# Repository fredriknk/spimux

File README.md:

# spimux

 <!-- 3D rendered pretty view -->

INFO INFO

[PCB layout](./DOCUMENTATION/spimux_board_prints.pdf) <!-- PDFs of boards -->
[SCHEMATIC](./DOCUMENTATION/spimux_schematic.pdf) <!-- Schematic PDFs -->

## FRONT

## BACK

## SIDE

# Before major commmits
Remember to run generate_outputs.bat/sh
to update the outputs and pictures.
readmetemplate

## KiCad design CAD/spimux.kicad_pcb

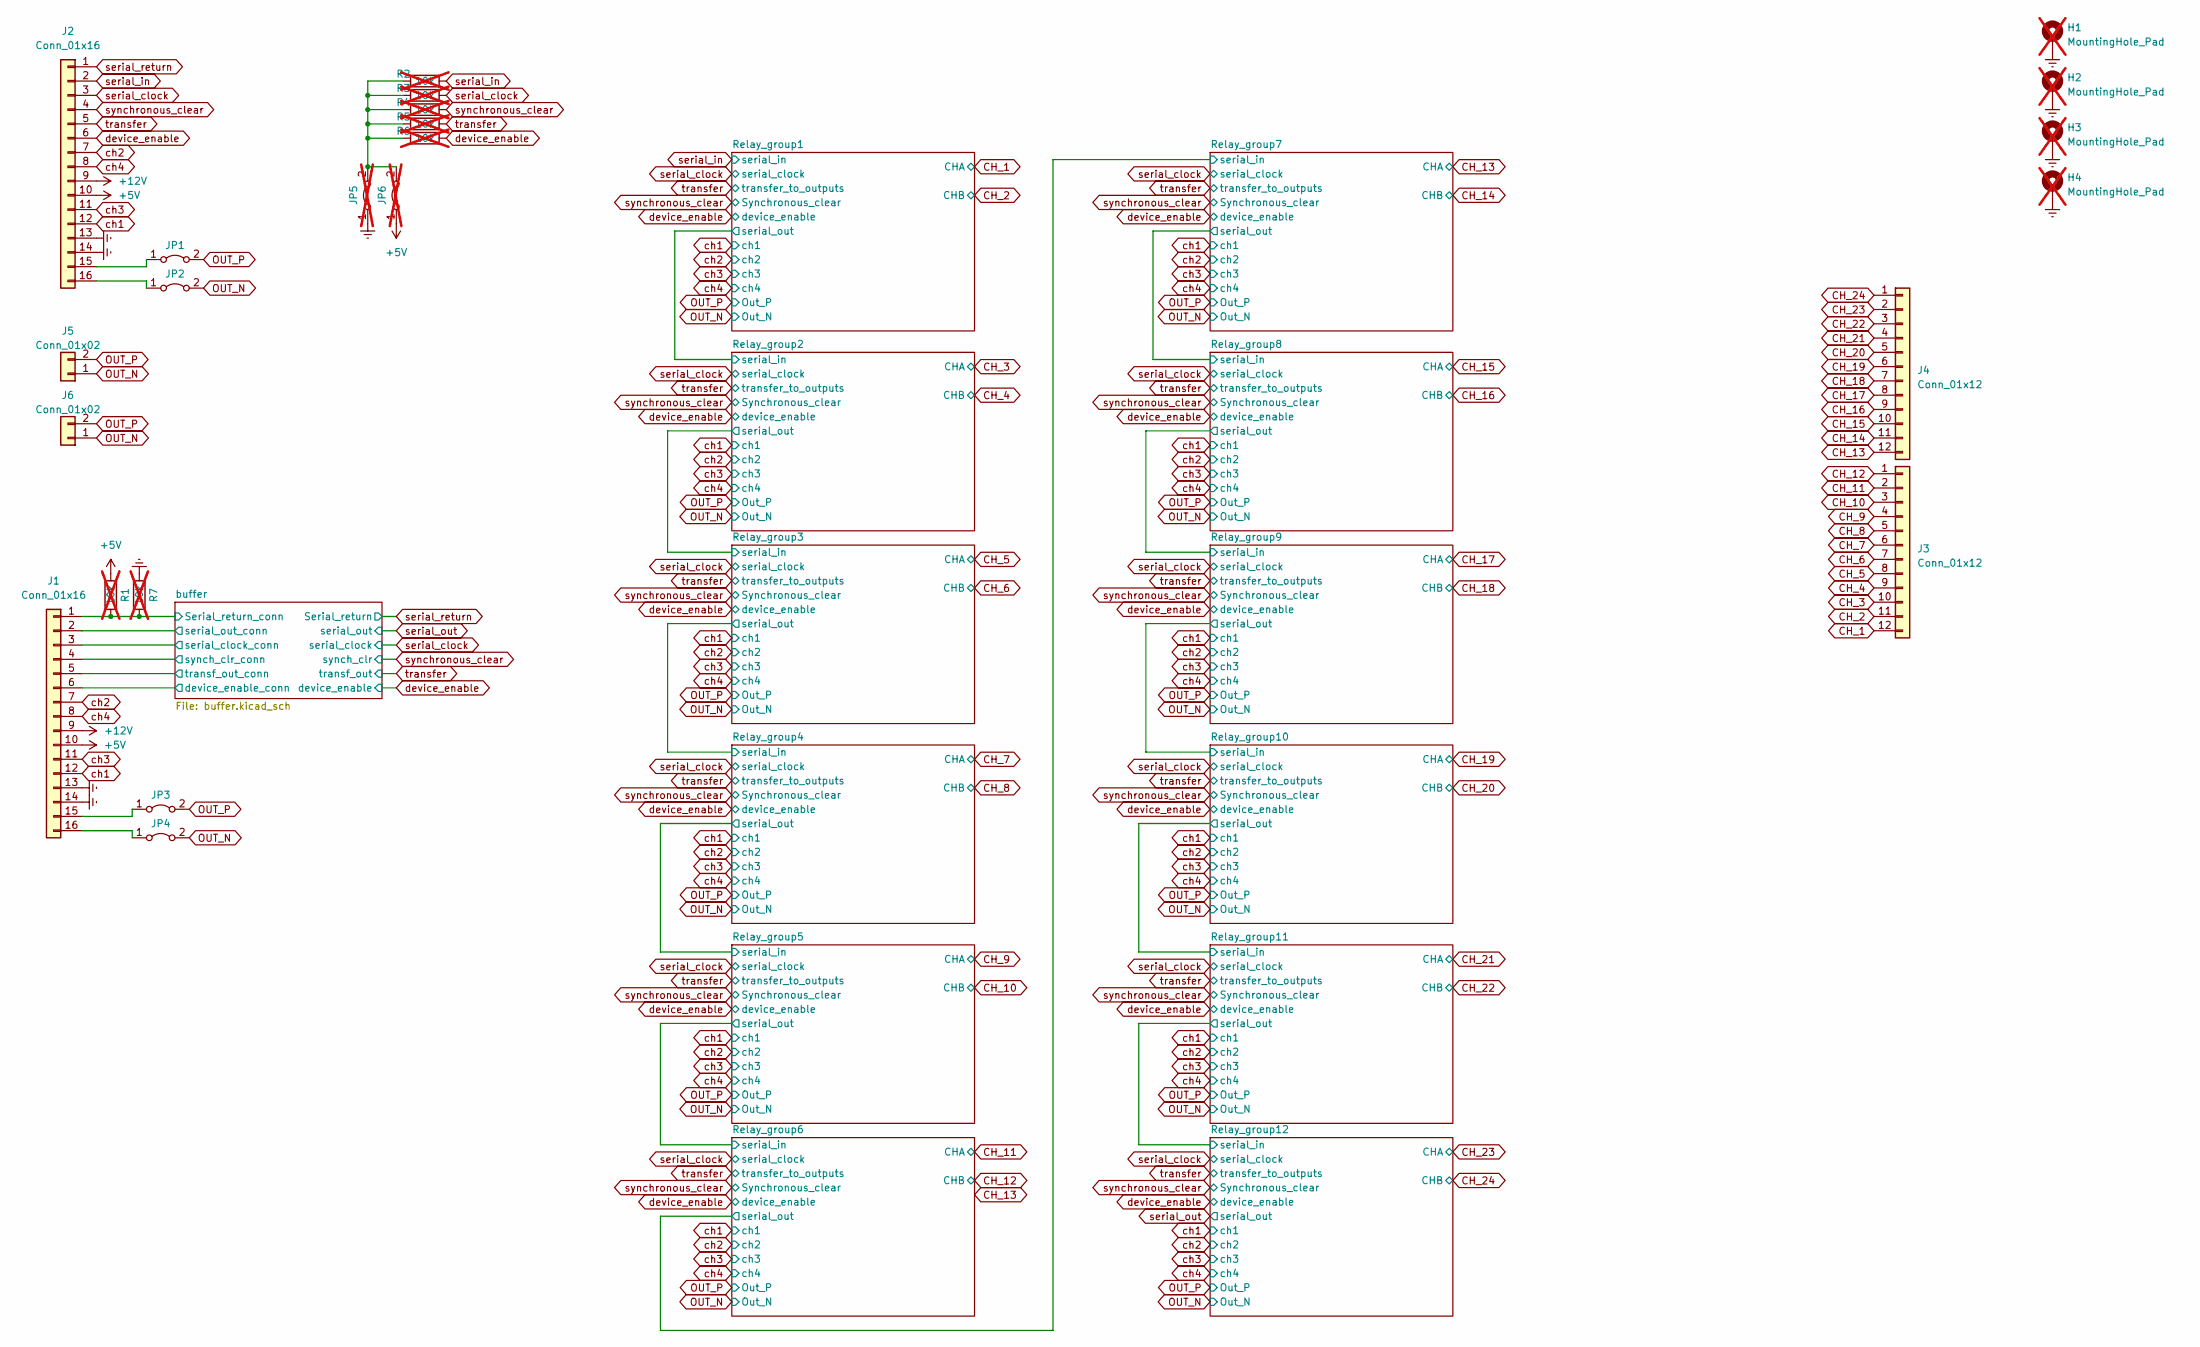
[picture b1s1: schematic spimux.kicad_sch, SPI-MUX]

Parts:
H1, H2, H3, H4: MountingHole_Pad; MountingHole_3.2mm_M3_Pad_Via; MPN NP; not fitted
J1, J2: Conn_01x16; IDC-Header_2x08_P2.54mm_Horizontal; MPN 3020-16-0200-00
J3, J4: Conn_01x12; New_PhoenixContact_MC_1,5_12-GF-5.08_1x12_P5.08mm_Horizonta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; MPN 1757349
J5, J6: Conn_01x02; New_PhoenixContact_MC_1,5_2-G-5.08_1x02_P5.08mm_Horizontal; MPN 1757242
JP1, JP2, JP3, JP4: Jumper_2_Bridged; R_0805_2012Metric; MPN 0805 0R JP
JP5, JP6: Jumper_2_Bridged; R_0603_1608Metric; MPN 0603 0R JP; not fitted
R1, R2, R3, R4, R5, R6, R7: 10k; R_0603_1608Metric; MPN 0603 10k 1%; not fitted

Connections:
+5V: J1.10, J2.10, JP6.1 (A), R1.1; also elsewhere on the board
+12V: J1.9, J2.9; also elsewhere on the board
/buffer/Serial_return_conn: J1.1, R1.2, R7.2; also elsewhere on the board
/buffer/device_enable_conn: J1.6; also elsewhere on the board
/buffer/serial_clock_conn: J1.3; also elsewhere on the board
/buffer/serial_out_conn: J1.2; also elsewhere on the board
/buffer/synch_clr_conn: J1.4; also elsewhere on the board
/buffer/transf_out_conn: J1.5; also elsewhere on the board
CH_1: J3.12; also elsewhere on the board
CH_2: J3.11; also elsewhere on the board
CH_3: J3.10; also elsewhere on the board
CH_4: J3.9; also elsewhere on the board
CH_5: J3.8; also elsewhere on the board
CH_6: J3.7; also elsewhere on the board
CH_7: J3.6; also elsewhere on the board
CH_8: J3.5; also elsewhere on the board
CH_9: J3.4; also elsewhere on the board
CH_10: J3.3; also elsewhere on the board
CH_11: J3.2; also elsewhere on the board
CH_12: J3.1; also elsewhere on the board
CH_13: J4.12; also elsewhere on the board
CH_14: J4.11; also elsewhere on the board
CH_15: J4.10; also elsewhere on the board
CH_16: J4.9; also elsewhere on the board
CH_17: J4.8; also elsewhere on the board
CH_18: J4.7; also elsewhere on the board
CH_19: J4.6; also elsewhere on the board
CH_20: J4.5; also elsewhere on the board
CH_21: J4.4; also elsewhere on the board
CH_22: J4.3; also elsewhere on the board
CH_23: J4.2; also elsewhere on the board
CH_24: J4.1; also elsewhere on the board
Earth: H1.1, H2.1, H3.1, H4.1, J1.13, J1.14, J2.13, J2.14, JP5.1 (A), R7.1; also elsewhere on the board
unnamed: J1.15, JP3.1 (A)
unnamed: J1.16, JP4.1 (A)
unnamed: J2.15, JP1.1 (A)
unnamed: J2.16, JP2.1 (A)
unnamed: JP5.2 (B), JP6.2 (B), R2.1, R3.1, R4.1, R5.1, R6.1
OUT_N: J5.1, J6.1, JP2.2 (B), JP4.2 (B); also elsewhere on the board
OUT_P: J5.2, J6.2, JP1.2 (B), JP3.2 (B); also elsewhere on the board
ch1: J1.12, J2.12; also elsewhere on the board
ch2: J1.7, J2.7; also elsewhere on the board
ch3: J1.11, J2.11; also elsewhere on the board
ch4: J1.8, J2.8; also elsewhere on the board
device_enable: J2.6, R6.2; also elsewhere on the board
serial_clock: J2.3, R3.2; also elsewhere on the board
serial_in: J2.2, R2.2; also elsewhere on the board
serial_return: J2.1; also elsewhere on the board
synchronous_clear: J2.4, R4.2; also elsewhere on the board
transfer: J2.5, R5.2; also elsewhere on the board

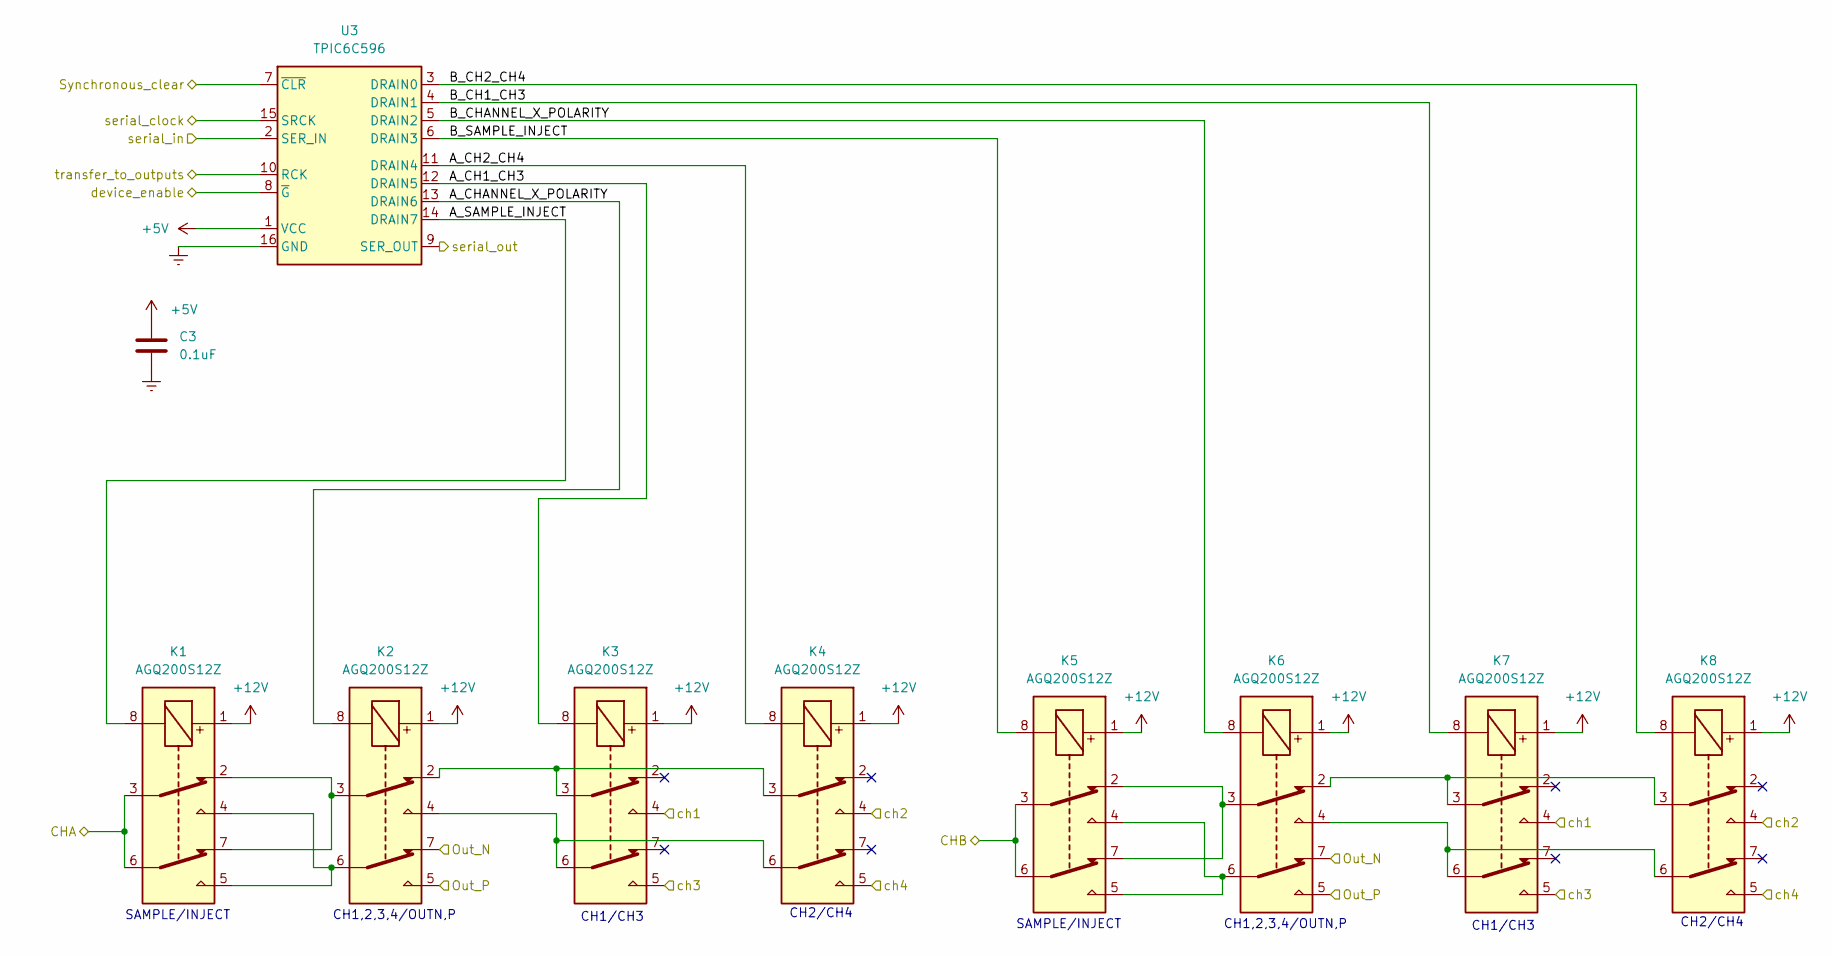
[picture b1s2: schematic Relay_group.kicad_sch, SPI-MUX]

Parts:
C3: 0.1uF; C_0603_1608Metric; MPN 0603 100nF 24v
K1, K2, K3, K4, K5, K6, K7, K8: AGQ200S12Z; Relay_2P2T_10x6mm_TE_IMxxG; MPN AGQ200S12Z
U3: TPIC6C596; TSSOP-16_4.4x5mm_P0.65mm; MPN TPIC6C596PWR

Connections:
+5V: C3.1, U3.1 (VCC); also elsewhere on the board
+12V: K1.1, K2.1, K3.1, K4.1, K5.1, K6.1, K7.1, K8.1; also elsewhere on the board
/Relay_group1/A_CH1_CH3: K3.8, U3.12 (DRAIN5)
/Relay_group1/A_CH2_CH4: K4.8, U3.11 (DRAIN4)
/Relay_group1/A_CHANNEL_X_POLARITY: K2.8, U3.13 (DRAIN6)
/Relay_group1/A_SAMPLE_INJECT: K1.8, U3.14 (DRAIN7)
/Relay_group1/B_CH1_CH3: K7.8, U3.4 (DRAIN1)
/Relay_group1/B_CH2_CH4: K8.8, U3.3 (DRAIN0)
/Relay_group1/B_CHANNEL_X_POLARITY: K6.8, U3.5 (DRAIN2)
/Relay_group1/B_SAMPLE_INJECT: K5.8, U3.6 (DRAIN3)
/Relay_group1/serial_out: U3.9 (SER_OUT); also elsewhere on the board
CH_1: K1.3, K1.6; also elsewhere on the board
CH_2: K5.3, K5.6; also elsewhere on the board
Earth: C3.2, U3.16 (GND); also elsewhere on the board
unnamed: K1.2, K1.7, K2.3
unnamed: K1.4, K1.5, K2.6
unnamed: K2.2, K3.3, K4.3
unnamed: K2.4, K3.6, K4.6
unnamed: K5.2, K5.7, K6.3
unnamed: K5.4, K5.5, K6.6
unnamed: K6.2, K7.3, K8.3
unnamed: K6.4, K7.6, K8.6
OUT_N: K2.7, K6.7; also elsewhere on the board
OUT_P: K2.5, K6.5; also elsewhere on the board
ch1: K3.4, K7.4; also elsewhere on the board
ch2: K4.4, K8.4; also elsewhere on the board
ch3: K3.5, K7.5; also elsewhere on the board
ch4: K4.5, K8.5; also elsewhere on the board
device_enable: U3.8 (~G); also elsewhere on the board
serial_clock: U3.15 (SRCK); also elsewhere on the board
serial_in: U3.2 (SER_IN); also elsewhere on the board
synchronous_clear: U3.7 (~CLR); also elsewhere on the board
transfer: U3.10 (RCK); also elsewhere on the board

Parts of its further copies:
C4, C5, C6, C7, C8, C9, C10, C11, C12, C13, C14: 0.1uF; C_0603_1608Metric; MPN 0603 100nF 24v
K9, K10, K11, K12, K13, K14, K15, K16, K17, K18, K19, K20, K21, K22, K23, K24, K25, K26, K27, K28, K29, K30, K31, K32, K33, K34, K35, K36, K37, K38, K39, K40, K41, K42, K43, K44, K45, K46, K47, K48, K49, K50, K51, K52, K53, K54, K55, K56, K57, K58, K59, K60, K61, K62, K63, K64, K65, K66, K67, K68, K69, K70, K71, K72, K73, K74, K75, K76, K77, K78, K79, K80, K81, K82, K83, K84, K85, K86, K87, K88, K89, K90, K91, K92, K93, K94, K95, K96: AGQ200S12Z; Relay_2P2T_10x6mm_TE_IMxxG; MPN AGQ200S12Z
U4, U5, U6, U7, U8, U9, U10, U11, U12, U13, U14: TPIC6C596; TSSOP-16_4.4x5mm_P0.65mm; MPN TPIC6C596PWR

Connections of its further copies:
+5V: C4.1, C5.1, C6.1, C7.1, C8.1, C9.1, C10.1, C11.1, C12.1, C13.1, C14.1, U4.1 (VCC), U5.1 (VCC), U6.1 (VCC), U7.1 (VCC), U8.1 (VCC), U9.1 (VCC), U10.1 (VCC), U11.1 (VCC), U12.1 (VCC), U13.1 (VCC), U14.1 (VCC); also elsewhere on the board
+12V: K9.1, K10.1, K11.1, K12.1, K13.1, K14.1, K15.1, K16.1, K17.1, K18.1, K19.1, K20.1, K21.1, K22.1, K23.1, K24.1, K25.1, K26.1, K27.1, K28.1, K29.1, K30.1, K31.1, K32.1, K33.1, K34.1, K35.1, K36.1, K37.1, K38.1, K39.1, K40.1, K41.1, K42.1, K43.1, K44.1, K45.1, K46.1, K47.1, K48.1, K49.1, K50.1, K51.1, K52.1, K53.1, K54.1, K55.1, K56.1, K57.1, K58.1, K59.1, K60.1, K61.1, K62.1, K63.1, K64.1, K65.1, K66.1, K67.1, K68.1, K69.1, K70.1, K71.1, K72.1, K73.1, K74.1, K75.1, K76.1, K77.1, K78.1, K79.1, K80.1, K81.1, K82.1, K83.1, K84.1, K85.1, K86.1, K87.1, K88.1, K89.1, K90.1, K91.1, K92.1, K93.1, K94.1, K95.1, K96.1; also elsewhere on the board
/Relay_group1/serial_out: U4.2 (SER_IN); also elsewhere on the board
/Relay_group2/A_CH1_CH3: K11.8, U4.12 (DRAIN5)
/Relay_group2/A_CH2_CH4: K12.8, U4.11 (DRAIN4)
/Relay_group2/A_CHANNEL_X_POLARITY: K10.8, U4.13 (DRAIN6)
/Relay_group2/A_SAMPLE_INJECT: K9.8, U4.14 (DRAIN7)
/Relay_group2/B_CH1_CH3: K15.8, U4.4 (DRAIN1)
/Relay_group2/B_CH2_CH4: K16.8, U4.3 (DRAIN0)
/Relay_group2/B_CHANNEL_X_POLARITY: K14.8, U4.5 (DRAIN2)
/Relay_group2/B_SAMPLE_INJECT: K13.8, U4.6 (DRAIN3)
/Relay_group2/serial_out: U4.9 (SER_OUT), U5.2 (SER_IN)
/Relay_group3/A_CH1_CH3: K19.8, U5.12 (DRAIN5)
/Relay_group3/A_CH2_CH4: K20.8, U5.11 (DRAIN4)
/Relay_group3/A_CHANNEL_X_POLARITY: K18.8, U5.13 (DRAIN6)
/Relay_group3/A_SAMPLE_INJECT: K17.8, U5.14 (DRAIN7)
/Relay_group3/B_CH1_CH3: K23.8, U5.4 (DRAIN1)
/Relay_group3/B_CH2_CH4: K24.8, U5.3 (DRAIN0)
/Relay_group3/B_CHANNEL_X_POLARITY: K22.8, U5.5 (DRAIN2)
/Relay_group3/B_SAMPLE_INJECT: K21.8, U5.6 (DRAIN3)
/Relay_group3/serial_out: U5.9 (SER_OUT), U6.2 (SER_IN)
/Relay_group4/A_CH1_CH3: K27.8, U6.12 (DRAIN5)
/Relay_group4/A_CH2_CH4: K28.8, U6.11 (DRAIN4)
/Relay_group4/A_CHANNEL_X_POLARITY: K26.8, U6.13 (DRAIN6)
/Relay_group4/A_SAMPLE_INJECT: K25.8, U6.14 (DRAIN7)
/Relay_group4/B_CH1_CH3: K31.8, U6.4 (DRAIN1)
/Relay_group4/B_CH2_CH4: K32.8, U6.3 (DRAIN0)
/Relay_group4/B_CHANNEL_X_POLARITY: K30.8, U6.5 (DRAIN2)
/Relay_group4/B_SAMPLE_INJECT: K29.8, U6.6 (DRAIN3)
/Relay_group4/serial_out: U6.9 (SER_OUT), U7.2 (SER_IN)
/Relay_group5/A_CH1_CH3: K35.8, U7.12 (DRAIN5)
/Relay_group5/A_CH2_CH4: K36.8, U7.11 (DRAIN4)
/Relay_group5/A_CHANNEL_X_POLARITY: K34.8, U7.13 (DRAIN6)
/Relay_group5/A_SAMPLE_INJECT: K33.8, U7.14 (DRAIN7)
/Relay_group5/B_CH1_CH3: K39.8, U7.4 (DRAIN1)
/Relay_group5/B_CH2_CH4: K40.8, U7.3 (DRAIN0)
/Relay_group5/B_CHANNEL_X_POLARITY: K38.8, U7.5 (DRAIN2)
/Relay_group5/B_SAMPLE_INJECT: K37.8, U7.6 (DRAIN3)
/Relay_group5/serial_out: U7.9 (SER_OUT), U8.2 (SER_IN)
/Relay_group6/A_CH1_CH3: K43.8, U8.12 (DRAIN5)
/Relay_group6/A_CH2_CH4: K44.8, U8.11 (DRAIN4)
/Relay_group6/A_CHANNEL_X_POLARITY: K42.8, U8.13 (DRAIN6)
/Relay_group6/A_SAMPLE_INJECT: K41.8, U8.14 (DRAIN7)
/Relay_group6/B_CH1_CH3: K47.8, U8.4 (DRAIN1)
/Relay_group6/B_CH2_CH4: K48.8, U8.3 (DRAIN0)
/Relay_group6/B_CHANNEL_X_POLARITY: K46.8, U8.5 (DRAIN2)
/Relay_group6/B_SAMPLE_INJECT: K45.8, U8.6 (DRAIN3)
/Relay_group6/serial_out: U8.9 (SER_OUT), U9.2 (SER_IN)
/Relay_group7/A_CH1_CH3: K51.8, U9.12 (DRAIN5)
/Relay_group7/A_CH2_CH4: K52.8, U9.11 (DRAIN4)
/Relay_group7/A_CHANNEL_X_POLARITY: K50.8, U9.13 (DRAIN6)
/Relay_group7/A_SAMPLE_INJECT: K49.8, U9.14 (DRAIN7)
/Relay_group7/B_CH1_CH3: K55.8, U9.4 (DRAIN1)
/Relay_group7/B_CH2_CH4: K56.8, U9.3 (DRAIN0)
/Relay_group7/B_CHANNEL_X_POLARITY: K54.8, U9.5 (DRAIN2)
/Relay_group7/B_SAMPLE_INJECT: K53.8, U9.6 (DRAIN3)
/Relay_group7/serial_out: U9.9 (SER_OUT), U10.2 (SER_IN)
/Relay_group8/A_CH1_CH3: K59.8, U10.12 (DRAIN5)
/Relay_group8/A_CH2_CH4: K60.8, U10.11 (DRAIN4)
/Relay_group8/A_CHANNEL_X_POLARITY: K58.8, U10.13 (DRAIN6)
/Relay_group8/A_SAMPLE_INJECT: K57.8, U10.14 (DRAIN7)
/Relay_group8/B_CH1_CH3: K63.8, U10.4 (DRAIN1)
/Relay_group8/B_CH2_CH4: K64.8, U10.3 (DRAIN0)
/Relay_group8/B_CHANNEL_X_POLARITY: K62.8, U10.5 (DRAIN2)
/Relay_group8/B_SAMPLE_INJECT: K61.8, U10.6 (DRAIN3)
/Relay_group8/serial_out: U10.9 (SER_OUT), U11.2 (SER_IN)
/Relay_group9/A_CH1_CH3: K67.8, U11.12 (DRAIN5)
/Relay_group9/A_CH2_CH4: K68.8, U11.11 (DRAIN4)
/Relay_group9/A_CHANNEL_X_POLARITY: K66.8, U11.13 (DRAIN6)
/Relay_group9/A_SAMPLE_INJECT: K65.8, U11.14 (DRAIN7)
/Relay_group9/B_CH1_CH3: K71.8, U11.4 (DRAIN1)
/Relay_group9/B_CH2_CH4: K72.8, U11.3 (DRAIN0)
/Relay_group9/B_CHANNEL_X_POLARITY: K70.8, U11.5 (DRAIN2)
/Relay_group9/B_SAMPLE_INJECT: K69.8, U11.6 (DRAIN3)
/Relay_group10/A_CH1_CH3: K75.8, U12.12 (DRAIN5)
/Relay_group10/A_CH2_CH4: K76.8, U12.11 (DRAIN4)
/Relay_group10/A_CHANNEL_X_POLARITY: K74.8, U12.13 (DRAIN6)
/Relay_group10/A_SAMPLE_INJECT: K73.8, U12.14 (DRAIN7)
/Relay_group10/B_CH1_CH3: K79.8, U12.4 (DRAIN1)
/Relay_group10/B_CH2_CH4: K80.8, U12.3 (DRAIN0)
/Relay_group10/B_CHANNEL_X_POLARITY: K78.8, U12.5 (DRAIN2)
/Relay_group10/B_SAMPLE_INJECT: K77.8, U12.6 (DRAIN3)
/Relay_group10/serial_in: U11.9 (SER_OUT), U12.2 (SER_IN)
/Relay_group10/serial_out: U12.9 (SER_OUT), U13.2 (SER_IN)
/Relay_group11/A_CH1_CH3: K83.8, U13.12 (DRAIN5)
/Relay_group11/A_CH2_CH4: K84.8, U13.11 (DRAIN4)
/Relay_group11/A_CHANNEL_X_POLARITY: K82.8, U13.13 (DRAIN6)
/Relay_group11/A_SAMPLE_INJECT: K81.8, U13.14 (DRAIN7)
/Relay_group11/B_CH1_CH3: K87.8, U13.4 (DRAIN1)
/Relay_group11/B_CH2_CH4: K88.8, U13.3 (DRAIN0)
/Relay_group11/B_CHANNEL_X_POLARITY: K86.8, U13.5 (DRAIN2)
/Relay_group11/B_SAMPLE_INJECT: K85.8, U13.6 (DRAIN3)
/Relay_group11/serial_out: U13.9 (SER_OUT), U14.2 (SER_IN)
/Relay_group12/A_CH1_CH3: K91.8, U14.12 (DRAIN5)
/Relay_group12/A_CH2_CH4: K92.8, U14.11 (DRAIN4)
/Relay_group12/A_CHANNEL_X_POLARITY: K90.8, U14.13 (DRAIN6)
/Relay_group12/A_SAMPLE_INJECT: K89.8, U14.14 (DRAIN7)
/Relay_group12/B_CH1_CH3: K95.8, U14.4 (DRAIN1)
/Relay_group12/B_CH2_CH4: K96.8, U14.3 (DRAIN0)
/Relay_group12/B_CHANNEL_X_POLARITY: K94.8, U14.5 (DRAIN2)
/Relay_group12/B_SAMPLE_INJECT: K93.8, U14.6 (DRAIN3)
CH_3: K9.3, K9.6; also elsewhere on the board
CH_4: K13.3, K13.6; also elsewhere on the board
CH_5: K17.3, K17.6; also elsewhere on the board
CH_6: K21.3, K21.6; also elsewhere on the board
CH_7: K25.3, K25.6; also elsewhere on the board
CH_8: K29.3, K29.6; also elsewhere on the board
CH_9: K33.3, K33.6; also elsewhere on the board
CH_10: K37.3, K37.6; also elsewhere on the board
CH_11: K41.3, K41.6; also elsewhere on the board
CH_12: K45.3, K45.6; also elsewhere on the board
CH_13: K49.3, K49.6; also elsewhere on the board
CH_14: K53.3, K53.6; also elsewhere on the board
CH_15: K57.3, K57.6; also elsewhere on the board
CH_16: K61.3, K61.6; also elsewhere on the board
CH_17: K65.3, K65.6; also elsewhere on the board
CH_18: K69.3, K69.6; also elsewhere on the board
CH_19: K73.3, K73.6; also elsewhere on the board
CH_20: K77.3, K77.6; also elsewhere on the board
CH_21: K81.3, K81.6; also elsewhere on the board
CH_22: K85.3, K85.6; also elsewhere on the board
CH_23: K89.3, K89.6; also elsewhere on the board
CH_24: K93.3, K93.6; also elsewhere on the board
Earth: C4.2, C5.2, C6.2, C7.2, C8.2, C9.2, C10.2, C11.2, C12.2, C13.2, C14.2, U4.16 (GND), U5.16 (GND), U6.16 (GND), U7.16 (GND), U8.16 (GND), U9.16 (GND), U10.16 (GND), U11.16 (GND), U12.16 (GND), U13.16 (GND), U14.16 (GND); also elsewhere on the board
unnamed: K10.2, K11.3, K12.3
unnamed: K9.2, K9.7, K10.3
unnamed: K10.4, K11.6, K12.6
unnamed: K9.4, K9.5, K10.6
unnamed: K13.2, K13.7, K14.3
unnamed: K13.4, K13.5, K14.6
unnamed: K14.2, K15.3, K16.3
unnamed: K14.4, K15.6, K16.6
unnamed: K17.2, K17.7, K18.3
unnamed: K17.4, K17.5, K18.6
unnamed: K18.2, K19.3, K20.3
unnamed: K18.4, K19.6, K20.6
unnamed: K21.2, K21.7, K22.3
unnamed: K21.4, K21.5, K22.6
unnamed: K22.2, K23.3, K24.3
unnamed: K22.4, K23.6, K24.6
unnamed: K25.2, K25.7, K26.3
unnamed: K25.4, K25.5, K26.6
unnamed: K26.2, K27.3, K28.3
unnamed: K26.4, K27.6, K28.6
unnamed: K29.2, K29.7, K30.3
unnamed: K29.4, K29.5, K30.6
unnamed: K30.2, K31.3, K32.3
unnamed: K30.4, K31.6, K32.6
unnamed: K33.2, K33.7, K34.3
unnamed: K33.4, K33.5, K34.6
unnamed: K34.2, K35.3, K36.3
unnamed: K34.4, K35.6, K36.6
unnamed: K37.2, K37.7, K38.3
unnamed: K37.4, K37.5, K38.6
unnamed: K38.2, K39.3, K40.3
unnamed: K38.4, K39.6, K40.6
unnamed: K41.2, K41.7, K42.3
unnamed: K41.4, K41.5, K42.6
unnamed: K42.2, K43.3, K44.3
unnamed: K42.4, K43.6, K44.6
unnamed: K45.2, K45.7, K46.3
unnamed: K45.4, K45.5, K46.6
unnamed: K46.2, K47.3, K48.3
unnamed: K46.4, K47.6, K48.6
unnamed: K49.2, K49.7, K50.3
unnamed: K49.4, K49.5, K50.6
unnamed: K50.2, K51.3, K52.3
unnamed: K50.4, K51.6, K52.6
unnamed: K53.2, K53.7, K54.3
unnamed: K53.4, K53.5, K54.6
unnamed: K54.2, K55.3, K56.3
unnamed: K54.4, K55.6, K56.6
unnamed: K57.2, K57.7, K58.3
unnamed: K57.4, K57.5, K58.6
unnamed: K58.2, K59.3, K60.3
unnamed: K58.4, K59.6, K60.6
unnamed: K61.2, K61.7, K62.3
unnamed: K61.4, K61.5, K62.6
unnamed: K62.2, K63.3, K64.3
unnamed: K62.4, K63.6, K64.6
unnamed: K65.2, K65.7, K66.3
unnamed: K65.4, K65.5, K66.6
unnamed: K66.2, K67.3, K68.3
unnamed: K66.4, K67.6, K68.6
unnamed: K69.2, K69.7, K70.3
unnamed: K69.4, K69.5, K70.6
unnamed: K70.2, K71.3, K72.3
unnamed: K70.4, K71.6, K72.6
unnamed: K73.2, K73.7, K74.3
unnamed: K73.4, K73.5, K74.6
unnamed: K74.2, K75.3, K76.3
unnamed: K74.4, K75.6, K76.6
unnamed: K77.2, K77.7, K78.3
unnamed: K77.4, K77.5, K78.6
unnamed: K78.2, K79.3, K80.3
unnamed: K78.4, K79.6, K80.6
unnamed: K81.2, K81.7, K82.3
unnamed: K81.4, K81.5, K82.6
unnamed: K82.2, K83.3, K84.3
unnamed: K82.4, K83.6, K84.6
unnamed: K85.2, K85.7, K86.3
unnamed: K85.4, K85.5, K86.6
unnamed: K86.2, K87.3, K88.3
unnamed: K86.4, K87.6, K88.6
unnamed: K89.2, K89.7, K90.3
unnamed: K89.4, K89.5, K90.6
unnamed: K90.2, K91.3, K92.3
unnamed: K90.4, K91.6, K92.6
unnamed: K93.2, K93.7, K94.3
unnamed: K93.4, K93.5, K94.6
unnamed: K94.2, K95.3, K96.3
unnamed: K94.4, K95.6, K96.6
OUT_N: K10.7, K14.7, K18.7, K22.7, K26.7, K30.7, K34.7, K38.7, K42.7, K46.7, K50.7, K54.7, K58.7, K62.7, K66.7, K70.7, K74.7, K78.7, K82.7, K86.7, K90.7, K94.7; also elsewhere on the board
OUT_P: K10.5, K14.5, K18.5, K22.5, K26.5, K30.5, K34.5, K38.5, K42.5, K46.5, K50.5, K54.5, K58.5, K62.5, K66.5, K70.5, K74.5, K78.5, K82.5, K86.5, K90.5, K94.5; also elsewhere on the board
ch1: K11.4, K15.4, K19.4, K23.4, K27.4, K31.4, K35.4, K39.4, K43.4, K47.4, K51.4, K55.4, K59.4, K63.4, K67.4, K71.4, K75.4, K79.4, K83.4, K87.4, K91.4, K95.4; also elsewhere on the board
ch2: K12.4, K16.4, K20.4, K24.4, K28.4, K32.4, K36.4, K40.4, K44.4, K48.4, K52.4, K56.4, K60.4, K64.4, K68.4, K72.4, K76.4, K80.4, K84.4, K88.4, K92.4, K96.4; also elsewhere on the board
ch3: K11.5, K15.5, K19.5, K23.5, K27.5, K31.5, K35.5, K39.5, K43.5, K47.5, K51.5, K55.5, K59.5, K63.5, K67.5, K71.5, K75.5, K79.5, K83.5, K87.5, K91.5, K95.5; also elsewhere on the board
ch4: K12.5, K16.5, K20.5, K24.5, K28.5, K32.5, K36.5, K40.5, K44.5, K48.5, K52.5, K56.5, K60.5, K64.5, K68.5, K72.5, K76.5, K80.5, K84.5, K88.5, K92.5, K96.5; also elsewhere on the board
device_enable: U4.8 (~G), U5.8 (~G), U6.8 (~G), U7.8 (~G), U8.8 (~G), U9.8 (~G), U10.8 (~G), U11.8 (~G), U12.8 (~G), U13.8 (~G), U14.8 (~G); also elsewhere on the board
serial_clock: U4.15 (SRCK), U5.15 (SRCK), U6.15 (SRCK), U7.15 (SRCK), U8.15 (SRCK), U9.15 (SRCK), U10.15 (SRCK), U11.15 (SRCK), U12.15 (SRCK), U13.15 (SRCK), U14.15 (SRCK); also elsewhere on the board
serial_out: U14.9 (SER_OUT); also elsewhere on the board
synchronous_clear: U4.7 (~CLR), U5.7 (~CLR), U6.7 (~CLR), U7.7 (~CLR), U8.7 (~CLR), U9.7 (~CLR), U10.7 (~CLR), U11.7 (~CLR), U12.7 (~CLR), U13.7 (~CLR), U14.7 (~CLR); also elsewhere on the board
transfer: U4.10 (RCK), U5.10 (RCK), U6.10 (RCK), U7.10 (RCK), U8.10 (RCK), U9.10 (RCK), U10.10 (RCK), U11.10 (RCK), U12.10 (RCK), U13.10 (RCK), U14.10 (RCK); also elsewhere on the board

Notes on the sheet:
CH1,2,3,4/OUTN,P
SAMPLE/INJECT
CH1/CH3
CH2/CH4

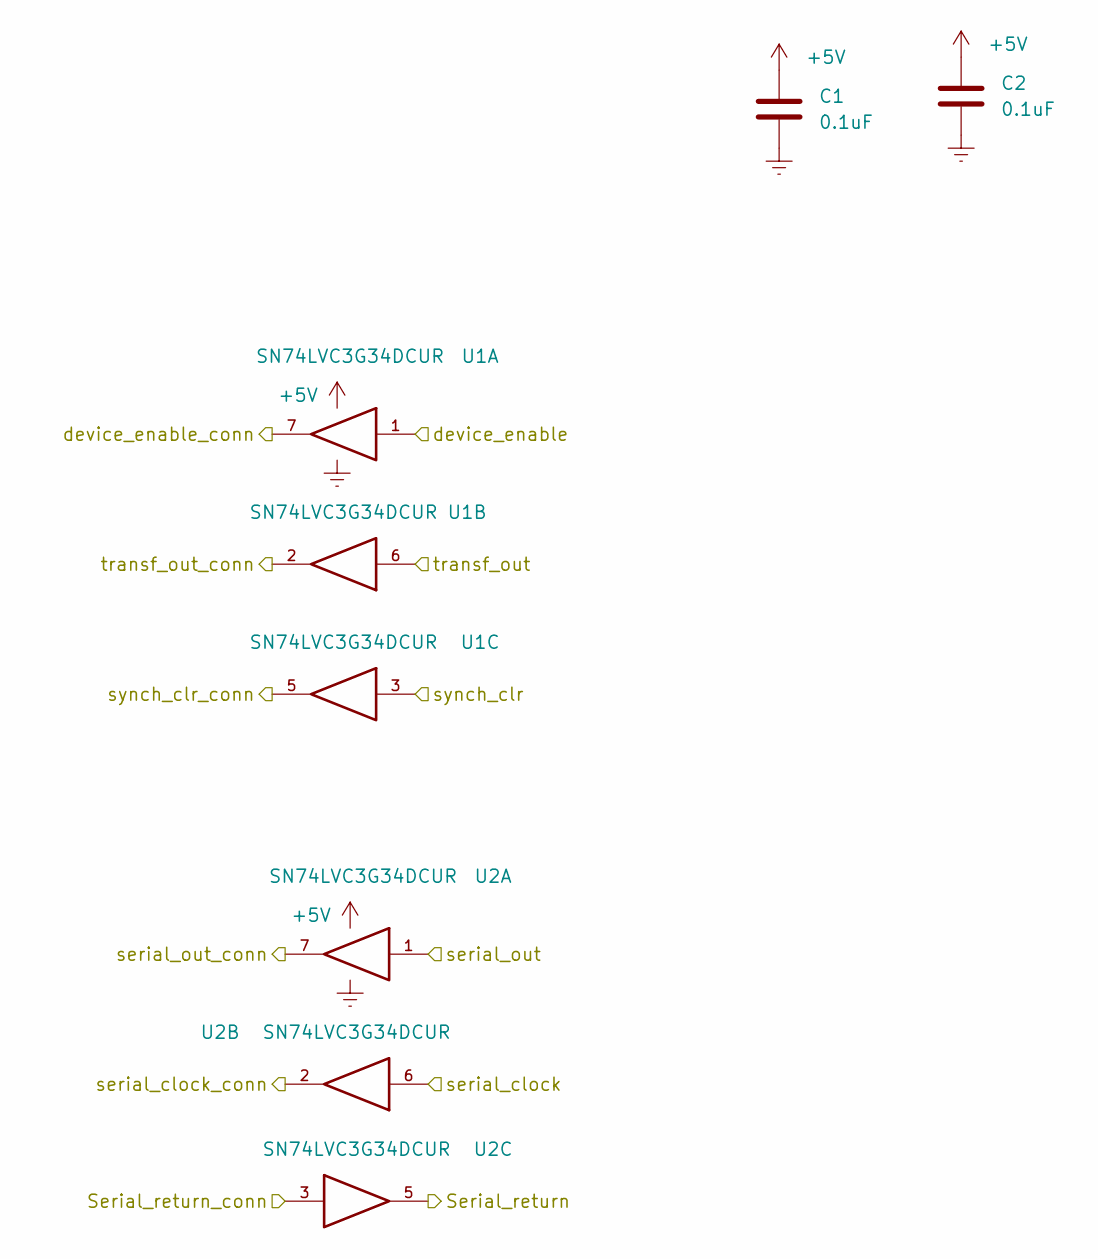
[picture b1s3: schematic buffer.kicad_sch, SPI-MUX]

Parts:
C1, C2: 0.1uF; C_0603_1608Metric; MPN 0603 100nF 24v
U1, U2: SN74LVC3G34DCUR; VSSOP-8_2.3x2mm_P0.5mm; MPN SN74LVC3G34DCUR

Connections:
+5V: C1.1, C2.1, U1.8 (VCC), U2.8 (VCC); also elsewhere on the board
/buffer/Serial_return_conn: U2.3; also elsewhere on the board
/buffer/device_enable_conn: U1.7; also elsewhere on the board
/buffer/serial_clock_conn: U2.2; also elsewhere on the board
/buffer/serial_out_conn: U2.7; also elsewhere on the board
/buffer/synch_clr_conn: U1.5; also elsewhere on the board
/buffer/transf_out_conn: U1.2; also elsewhere on the board
Earth: C1.2, C2.2, U1.4 (GND), U2.4 (GND); also elsewhere on the board
device_enable: U1.1; also elsewhere on the board
serial_clock: U2.6; also elsewhere on the board
serial_out: U2.1; also elsewhere on the board
serial_return: U2.5; also elsewhere on the board
synchronous_clear: U1.3; also elsewhere on the board
transfer: U1.6; also elsewhere on the board

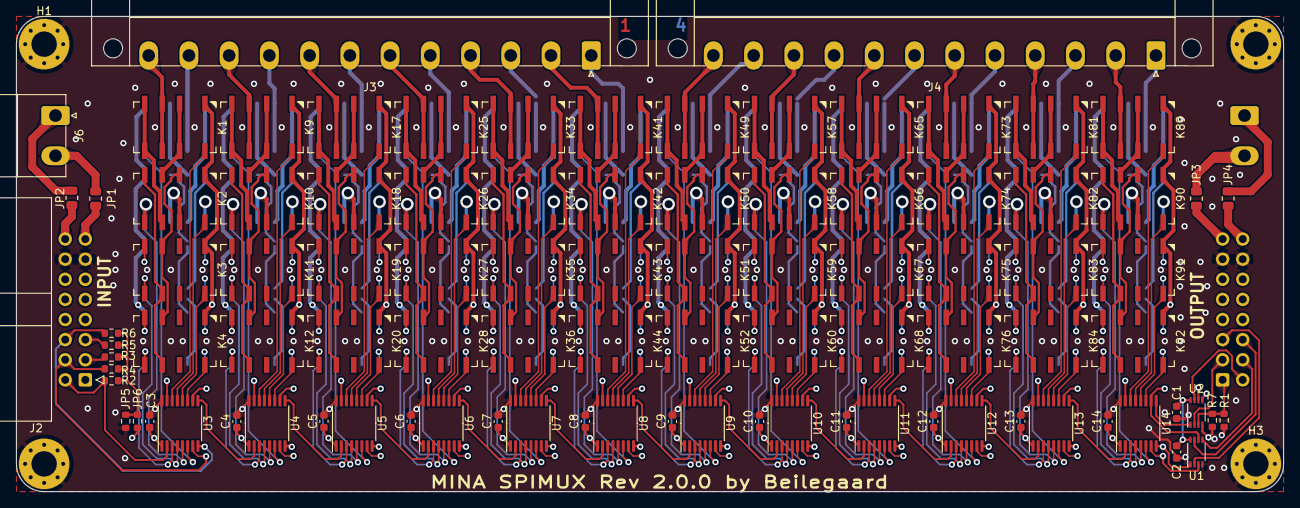
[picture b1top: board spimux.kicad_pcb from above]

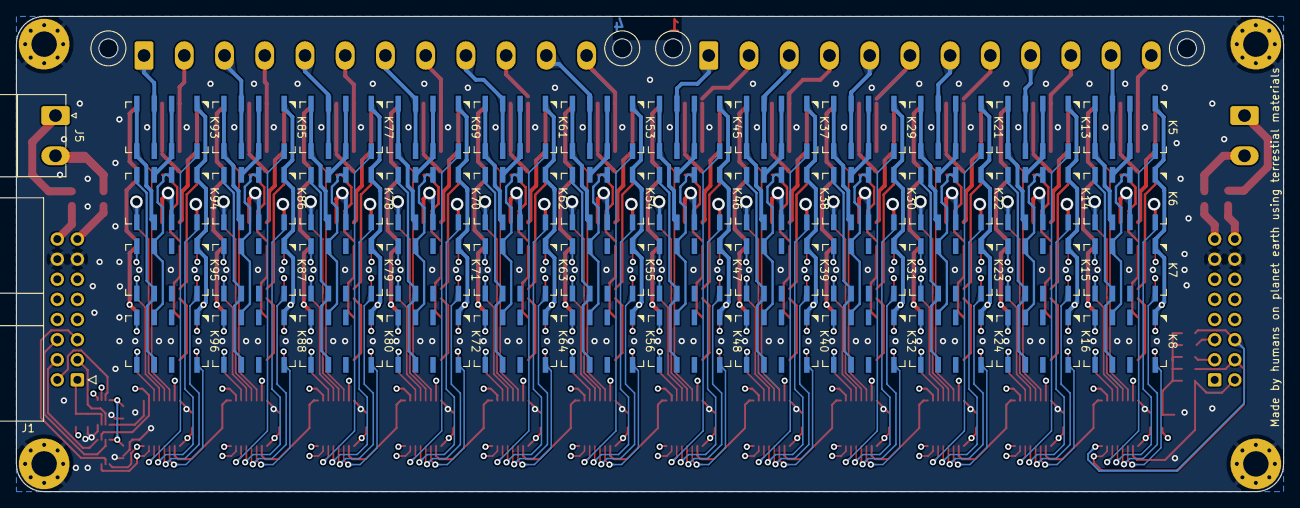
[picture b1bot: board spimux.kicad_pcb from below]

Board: 4 copper layers, 160.0 x 60.0 mm, 147 parts (50 on the bottom side), 254 nets.

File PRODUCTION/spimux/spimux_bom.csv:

"Refs","Value","Footprint","Qty","Manufacturer","MPN","Datasheet","DNP"
"C1-C14","0.1uF","Capacitor_SMD:C_0603_1608Metric","14","","0603 100nF 24v","~",""
"J1,J2","Conn_01x16","Connector_IDC:IDC-Header_2x08_P2.54mm_Horizontal","2","","3020-16-0200-00","~",""
"J3,J4","Conn_01x12","muxlib_footprints:New_PhoenixContact_MC_1,5_12-GF-5.08_1x12_P5.08mm_Horizontal_ThreadedFlange_MountHole","2","","1757349","~",""
"J5,J6","Conn_01x02","muxlib_footprints:New_PhoenixContact_MC_1,5_2-G-5.08_1x02_P5.08mm_Horizontal","2","","1757242","~",""
"JP1-JP4","Jumper_2_Bridged","Resistor_SMD:R_0805_2012Metric","4","","0805 0R JP","~",""
"JP5,JP6","Jumper_2_Bridged","Resistor_SMD:R_0603_1608Metric","2","","0603 0R JP","~","DNP"
"K1-K96","AGQ200S12Z","muxlib_footprints:Relay_2P2T_10x6mm_TE_IMxxG","96","","AGQ200S12Z","https://media.digikey.com/pdf/Data%20Sheets/Panasonic%20Elec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",""
"R1-R7","10k","Resistor_SMD:R_0603_1608Metric","7","","0603 10k 1%","~","DNP"
"U1,U2","SN74LVC3G34DCUR","Package_SO:VSSOP-8_2.3x2mm_P0.5mm","2","","SN74LVC3G34DCUR","https://www.ti.com/lit/ds/symlink/sn74lvc3g34.pdf?HQS=dis-dk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",""
"U3-U14","TPIC6C596","Package_SO:TSSOP-16_4.4x5mm_P0.65mm","12","","TPIC6C596PWR","https://www.ti.com/lit/ds/symlink/tpic6c596.pdf?HQS=dis-dk-n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",""

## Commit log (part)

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2023-02-06 new relays
2023-02-06 Feat:Added picture to readme
2023-02-06 fix:readme
2023-02-07 fix:readme ibom
2023-02-07 fix:ibom
2023-02-07 Feat:Fixed spi output marking
2023-02-07 Feat:Fixed digikey partnumbers, rexport, 3d mod
2023-02-15 Fix: I suck at proofreading
2023-05-05 Feat: Single side test
2023-05-05 Feat: WIP
2023-05-08 Feat:WIP push
